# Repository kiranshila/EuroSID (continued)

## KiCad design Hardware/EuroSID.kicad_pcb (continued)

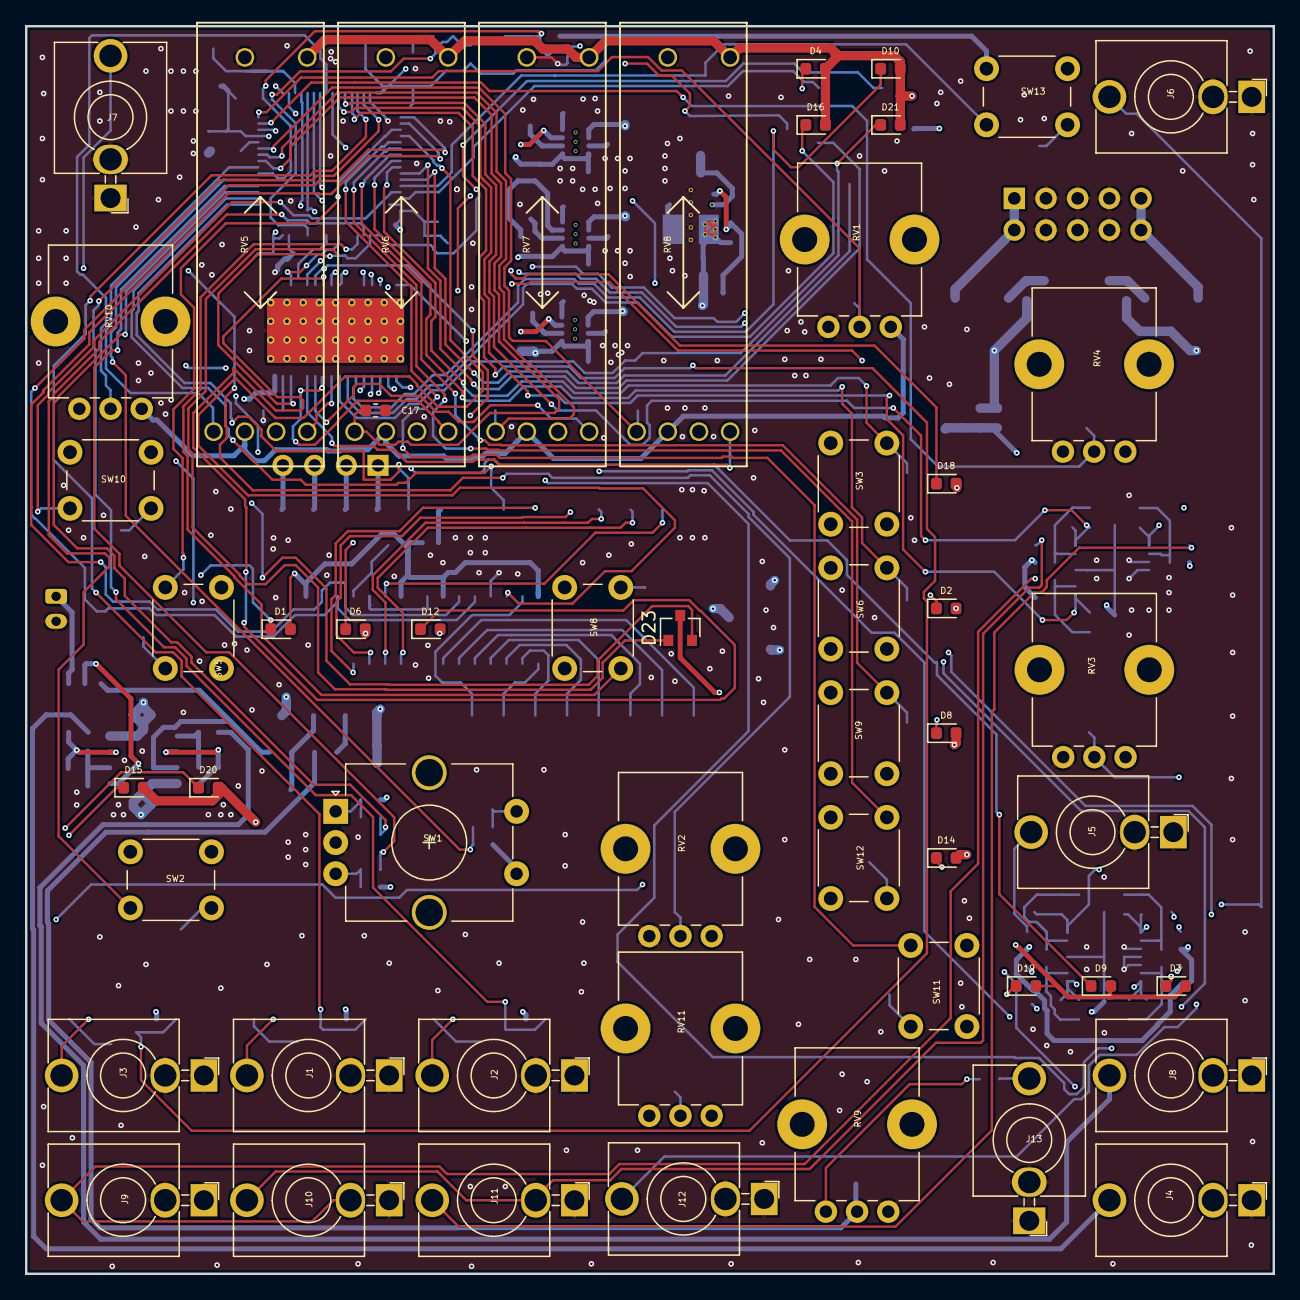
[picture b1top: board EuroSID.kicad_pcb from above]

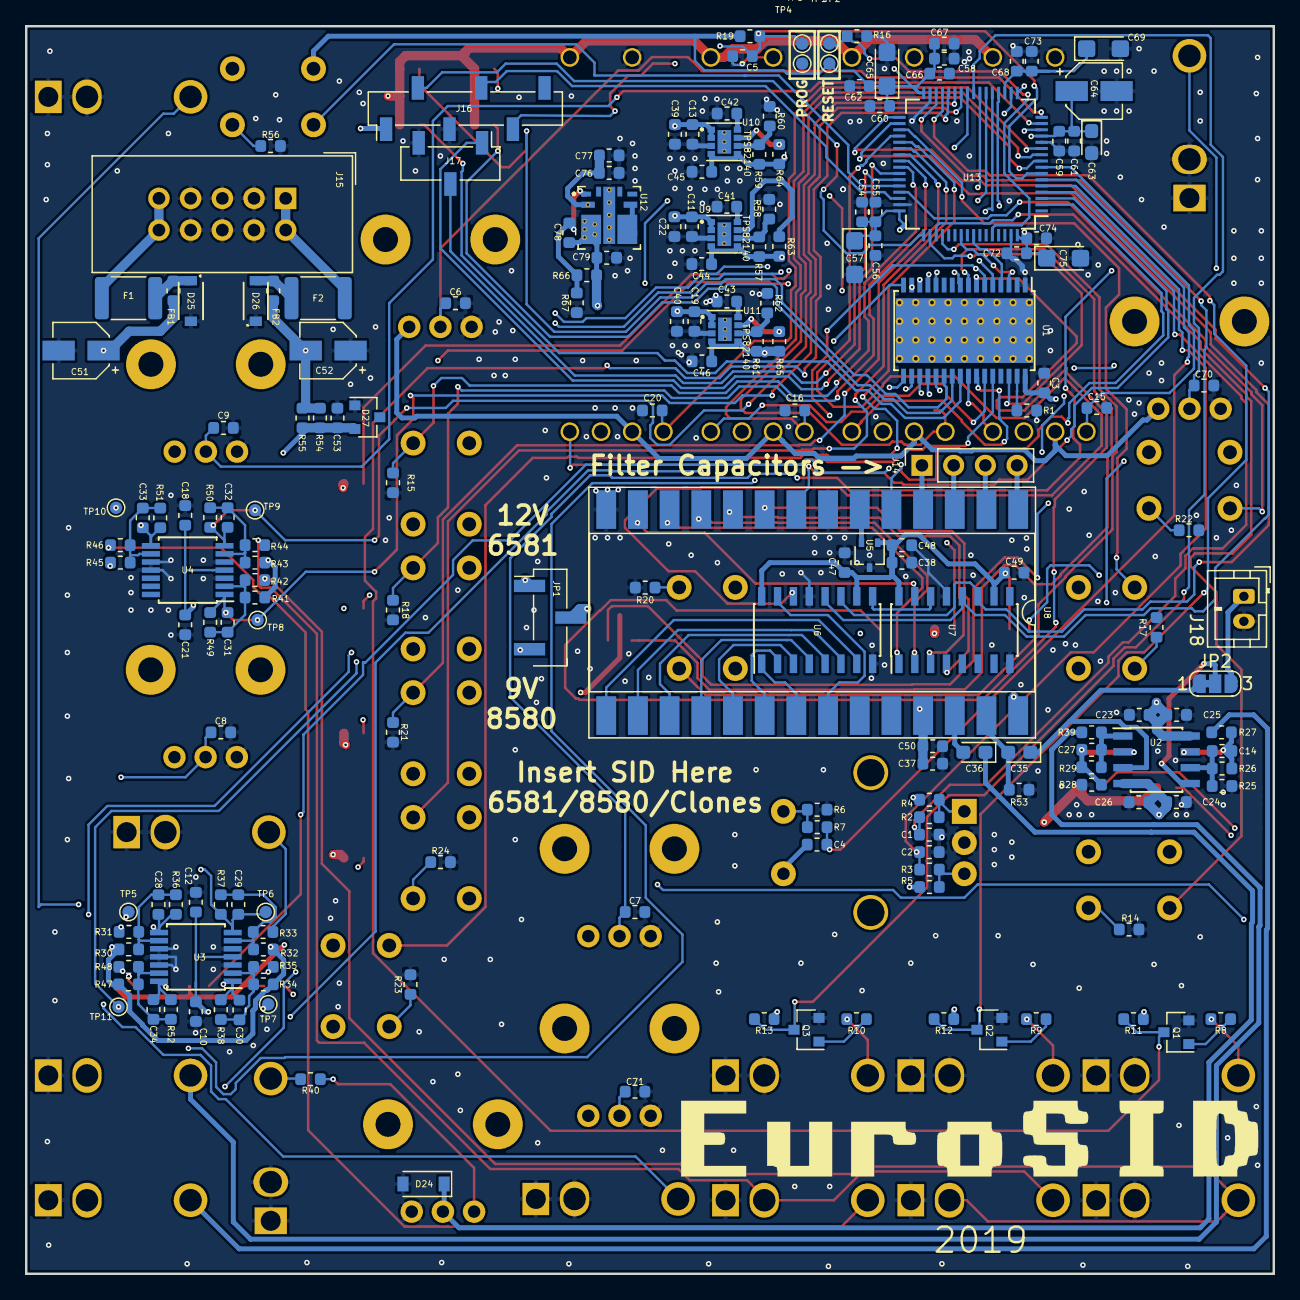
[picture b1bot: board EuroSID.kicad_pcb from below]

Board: 4 copper layers, 100.0 x 100.0 mm, 240 parts (187 on the bottom side), 150 nets.

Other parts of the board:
C76, C77: 10 uF; C_0603_1608Metric
C78: 330 pF; C_0603_1608Metric
C79: 22 uF; C_0603_1608Metric
R66: 10k; R_0603_1608Metric
R67: 2.2k; R_0603_1608Metric
U12: TPSM84209RKHT; VREG_TPSM84209RKHT

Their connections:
+9V: C78.1, C79.1, R66.2, U12.3, U12.VOUT1, U12.VOUT2, U12.VOUT3, U12.VOUT4, U12.VOUT5; also elsewhere on the board
+12V: C76.1, C77.1, U12.2, U12.VIN; also elsewhere on the board
GND: C76.2, C77.2, C79.2, R67.1, U12.8, U12.GND1, U12.GND2, U12.GND3, U12.GND4, U12.GND5; also elsewhere on the board
unnamed: C78.2, R66.1, R67.2, U12.1
unnamed: U12.4, U12.5

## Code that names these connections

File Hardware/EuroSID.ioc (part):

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Mcu.Name=STM32F303R(B-C)Tx
Mcu.Package=LQFP64
Mcu.UserName=STM32F303RBTx
PA0.GPIOParameters=GPIO_Label
PA0.GPIO_Label=PWM
PA0.Mode=IN1-Single-Ended
PA0.Signal=ADC1_IN1
PA1.GPIOParameters=GPIO_Label
PA1.GPIO_Label=CUTOFF
PA1.Mode=IN2-Single-Ended
PA1.Signal=ADC1_IN2
PA10.GPIOParameters=GPIO_Label
PA10.GPIO_Label=RX
PA10.Mode=Asynchronous
PA10.Signal=USART1_RX
PA11.GPIOParameters=GPIO_Label
PA11.GPIO_Label=SHAPE_SW
PA11.Signal=GPIO_Input
PA12.GPIOParameters=GPIO_Label
PA12.GPIO_Label=SET_SW
PA12.Signal=GPIO_Input
PA13.GPIOParameters=GPIO_Label
PA13.GPIO_Label=SWDIO
PA13.Mode=Serial_Wire
PA13.Signal=SYS_JTMS-SWDIO
PA14.GPIOParameters=GPIO_Label
PA14.GPIO_Label=SWCLK
PA14.Mode=Serial_Wire
PA14.Signal=SYS_JTCK-SWCLK
PA15.GPIOParameters=GPIO_Label
PA15.GPIO_Label=LED_LATCH
PA15.Mode=NSS_Signal_Hard_Output
PA15.Signal=SPI1_NSS
PA2.GPIOParameters=GPIO_Label
PA2.GPIO_Label=RESONANCE
PA2.Mode=IN3-Single-Ended
PA2.Signal=ADC1_IN3
PA3.GPIOParameters=GPIO_Label
PA3.GPIO_Label=FREQ_ATTEN
PA3.Mode=IN4-Single-Ended
PA3.Signal=ADC1_IN4
PA4.GPIOParameters=GPIO_Label
PA4.GPIO_Label=SHAPE_CV
PA4.Mode=IN1-Single-Ended
PA4.Signal=ADC2_IN1
PA5.GPIOParameters=GPIO_Label
PA5.GPIO_Label=PWM_CV
PA5.Mode=IN2-Single-Ended
PA5.Signal=ADC2_IN2
PA6.GPIOParameters=GPIO_Label
PA6.GPIO_Label=PWM_ATTEN
PA6.Mode=IN3-Single-Ended
PA6.Signal=ADC2_IN3
PA7.GPIOParameters=GPIO_Label
PA7.GPIO_Label=SET_CV
PA7.Mode=IN4-Single-Ended
PA7.Signal=ADC2_IN4
PA8.GPIOParameters=GPIO_Label
PA8.GPIO_Label=FILTER1_SW
PA8.Signal=GPIO_Input
PA9.GPIOParameters=GPIO_Label
PA9.GPIO_Label=TX
PA9.Mode=Asynchronous
PA9.Signal=USART1_TX
PB0.GPIOParameters=GPIO_Label
PB0.GPIO_Label=IN1_CV
PB0.Mode=IN12-Single-Ended
PB0.Signal=ADC3_IN12
PB1.GPIOParameters=GPIO_Label
PB1.GPIO_Label=IN2_CV
PB1.Mode=IN1-Single-Ended
PB1.Signal=ADC3_IN1
PB10.GPIOParameters=GPIO_Label
PB10.GPIO_Label=GATE_2
PB10.Signal=GPIO_Input
PB11.GPIOParameters=GPIO_Label
PB11.GPIO_Label=GATE_3
PB11.Signal=GPIO_Input
PB12.GPIOParameters=GPIO_Label
PB12.GPIO_Label=SID_LATCH
PB12.Mode=NSS_Signal_Hard_Output
PB12.Signal=SPI2_NSS
PB13.GPIOParameters=GPIO_Label
PB13.GPIO_Label=SID_CLK
PB13.Mode=TX_Only_Simplex_Unidirect_Master
PB13.Signal=SPI2_SCK
PB14.GPIOParameters=GPIO_Label
PB14.GPIO_Label=VOICE_SW
PB14.Signal=GPIO_Input
PB15.GPIOParameters=GPIO_Label
PB15.GPIO_Label=SID_DATA
PB15.Mode=TX_Only_Simplex_Unidirect_Master
PB15.Signal=SPI2_MOSI
PB2.GPIOParameters=GPIO_Label
PB2.GPIO_Label=GATE_1
PB2.Signal=GPIO_Input
PB3.GPIOParameters=GPIO_Label
PB3.GPIO_Label=LED_CLK
PB3.Mode=TX_Only_Simplex_Unidirect_Master
PB3.Signal=SPI1_SCK
PB5.GPIOParameters=GPIO_Label
PB5.GPIO_Label=LED_DATA
PB5.Mode=TX_Only_Simplex_Unidirect_Master
PB5.Signal=SPI1_MOSI
PC0.GPIOParameters=GPIO_Label
PC0.GPIO_Label=ATTACK
PC0.Signal=ADCx_IN6
PC1.GPIOParameters=GPIO_Label
PC1.GPIO_Label=DECAY
PC1.Signal=ADCx_IN7
PC10.GPIOParameters=GPIO_Label
PC10.GPIO_Label=MOD_SW
PC10.Signal=GPIO_Input
PC11.GPIOParameters=GPIO_Label
PC11.GPIO_Label=MODE_SW
PC11.Signal=GPIO_Input
PC13.GPIOParameters=GPIO_Label
PC13.GPIO_Label=SID_RES
PC13.Signal=GPIO_Input
PC14-OSC32_IN.GPIOParameters=GPIO_Label
PC14-OSC32_IN.GPIO_Label=SID_CS
PC14-OSC32_IN.Signal=GPIO_Input
PC15-OSC32_OUT.GPIOParameters=GPIO_Label
PC15-OSC32_OUT.GPIO_Label=FREQ_A
PC15-OSC32_OUT.Signal=GPIO_Input
PC2.GPIOParameters=GPIO_Label
PC2.GPIO_Label=SUSTAIN
PC2.Signal=ADCx_IN8
PC3.GPIOParameters=GPIO_Label
PC3.GPIO_Label=RELEASE
PC3.Signal=ADCx_IN9
PC4.GPIOParameters=GPIO_Label
PC4.GPIO_Label=SET_ATTEN
PC4.Mode=IN5-Single-Ended
PC4.Signal=ADC2_IN5
PC5.GPIOParameters=GPIO_Label
PC5.GPIO_Label=IN3_CV
PC5.Mode=IN11-Single-Ended
PC5.Signal=ADC2_IN11
PC6.GPIOParameters=GPIO_Label
PC6.GPIO_Label=FILTER_SW
PC6.Signal=GPIO_Input
PC7.GPIOParameters=GPIO_Label
PC7.GPIO_Label=FILTEREXT_SW
PC7.Signal=GPIO_Input
PC8.GPIOParameters=GPIO_Label
PC8.GPIO_Label=FILTER3_SW
PC8.Signal=GPIO_Input
PC9.GPIOParameters=GPIO_Label
PC9.GPIO_Label=FILTER2_SW
PC9.Signal=GPIO_Input
PF0-OSC_IN.GPIOParameters=GPIO_Label
PF0-OSC_IN.GPIO_Label=FREQ_B
PF0-OSC_IN.Signal=GPIO_Input
PF1-OSC_OUT.GPIOParameters=GPIO_Label
PF1-OSC_OUT.GPIO_Label=FREQ_SW
PF1-OSC_OUT.Signal=GPIO_Input
PF4.GPIOParameters=GPIO_Label
PF4.GPIO_Label=CUTOFF_CV
PF4.Mode=IN5-Single-Ended
PF4.Signal=ADC1_IN5
RCC.HSEPLLFreq_Value=8000000
RCC.HSE_VALUE=8000000
RCC.SYSCLKFreq_VALUE=64000000
RCC.SYSCLKSourceVirtual=RCC_SYSCLKSOURCE_PLLCLK
board=custom

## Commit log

2018-10-28 Added SIDTest.cpp
2018-11-01 Added Hardware
2018-11-01 Removed SIDTest.cpp
2018-11-02 Started board layout
2018-11-02 Added panel drawing
2018-11-02 Fixed issues with footprints
2018-11-02 Added PJ398SM model
2018-11-02 Added .gitignore
2018-11-02 Finished assigning footprints
2018-11-04 Changed MCU
2018-11-04 Updated schematic
2018-11-05 Added new MCU
2018-11-06 Finished updating MCU pinouts
2018-11-06 Fixed footprints for new attenuverter pots
2018-11-07 Board 1 Complete
2018-11-07 Seperated two board with headers
2018-11-07 Moved SID chip to backside
2018-11-07 Added standof holes
2018-11-08 Updated ADSR sliders
2018-11-08 Added 3D models
2018-11-09 Finished mechanical design on PCB
2018-11-09 Fixed location of headers for board to board
2018-11-09 Added some connector routing
2018-11-09 Removed SID1 and SID2 led
2018-11-09 Corrected layout and schematic to single standoff
2018-11-09 Couple traces
2018-11-10 Moved PWM CV
2018-11-10 Added 3D model of fader
2018-11-10 Routed 1st opamp, audio opamp
2018-11-10 Finishing up PCB
2018-11-11 Tried making board 100x100
2018-11-11 Updated panel drawing to be 100x100 PCB
2018-11-12 Updated PCBnew to reflect new panel layout
2018-11-12 More routing on IO board
2018-11-12 More wiring, removed pointless capacitors
2018-11-12 Finished PCB Layout
2018-11-13 Added silkscreen
2018-11-13 Swapped for real oscillator, fixed footprint discrepencies
2018-11-13 Generated Gerbers
2018-11-24 Generated STM32CubeMX code as a platformio project
2018-11-25 Fixes #10
2018-11-25 Cleaned up some traces, fixes #5
2018-11-25 Working on LED driver code
2019-03-08 STM32CubeMX Blinky
2019-03-08 LED Blink Works
2019-03-09 LED Driver Library
2019-03-10 IT WORKS
2019-03-10 Fixed some order of operations
2019-03-10 Fixed pwm order of operations
2019-03-11 Added filter testing code
2019-03-11 Updated to use multichannel DMA for the ADCs
2019-03-12 SID isn't working
2019-03-13 Fixed issue with GPIO setup and SID CS and RES pins
2019-03-13 Rm build
2019-03-13 Something is wrong with the DMA and CUTOFF_CV
2019-03-17 Updated to single four layer board
2019-03-23 Finalized 4 layer design, fixed bad opamp circuits
2019-03-28 Finished design of 4 layer, added stero option and logo
2019-04-20 Started state machine
2019-04-21 Progess
2019-04-23 More work
2019-04-26 Trying to get FreeRTOS to work
